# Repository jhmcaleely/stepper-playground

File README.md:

# stepper-playground

A scratch project to explore stepper motor control

Currently depends on:

- Pololu 2134, a carrier board for DRV8834 Stepper Driver
- Raspberry Pi Pico
- MicroPython

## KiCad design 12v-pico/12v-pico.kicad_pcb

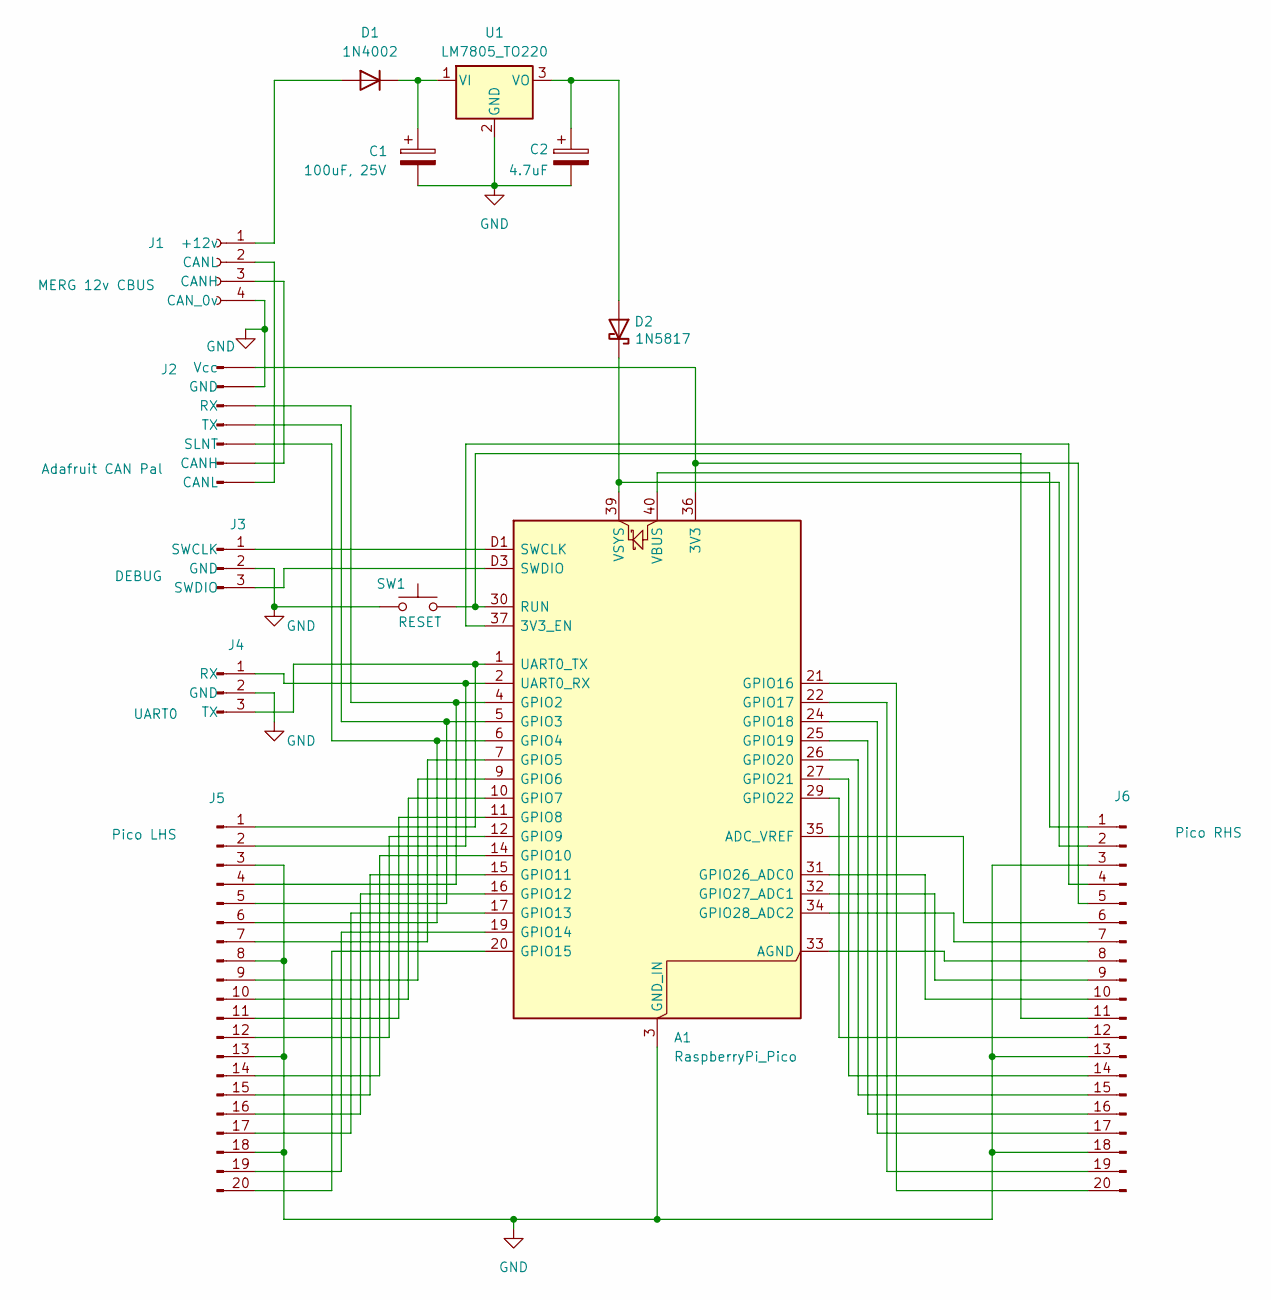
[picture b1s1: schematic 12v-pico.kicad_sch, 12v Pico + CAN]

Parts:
A1: RaspberryPi_Pico; RaspberryPi_Pico_SMD_HandSolder
C1: 100uF, 25V; CP_Radial_D4.0mm_P2.00mm
C2: 4.7uF; CP_Radial_Tantal_D4.5mm_P2.50mm
D1: 1N4002; D_DO-41_SOD81_P10.16mm_Horizontal
D2: 1N5817; D_DO-41_SOD81_P10.16mm_Horizontal
J1: MERG 12v CBUS; TerminalBlock_Phoenix_PT-1,5-4-3.5-H_1x04_P3.50mm_Horizontal
J2: Adafruit CAN Pal; PinHeader_1x07_P2.54mm_Vertical
J3: DEBUG; PinHeader_1x03_P2.54mm_Vertical
J4: UART0; PinSocket_1x03_P2.54mm_Vertical
J5: Pico LHS; PinHeader_1x20_P2.54mm_Vertical
J6: Pico RHS; PinHeader_1x20_P2.54mm_Vertical
SW1: RESET; SW_PUSH_6mm
U1: LM7805_TO220; TO-220-3_Vertical

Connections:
GND: A1.3 (GND_IN), A1.8 (GND), A1.13 (GND), A1.18 (GND), A1.23 (GND), A1.28 (GND), A1.38 (GND), A1.D2 (GND), C1.2, C2.2, J1.4 (CAN_0v), J2.2 (GND), J3.2 (GND), J4.2 (GND), J5.3, J5.8, J5.13, J5.18, J6.3, J6.13, J6.18, SW1.1, U1.2 (GND)
unnamed: A1.36 (3V3), J2.1 (Vcc), J6.5
unnamed: A1.37 (3V3_EN), J6.4
unnamed: A1.35 (ADC_VREF), J6.6
unnamed: A1.33 (AGND), J6.8
unnamed: A1.1 (UART0_TX), J4.3 (TX), J5.1
unnamed: A1.2 (UART0_RX), J4.1 (RX), J5.2
unnamed: A1.4 (GPIO2), J2.3 (RX), J5.4
unnamed: A1.5 (GPIO3), J2.4 (TX), J5.5
unnamed: A1.6 (GPIO4), J2.5 (SLNT), J5.6
unnamed: A1.7 (GPIO5), J5.7
unnamed: A1.9 (GPIO6), J5.9
unnamed: A1.10 (GPIO7), J5.10
unnamed: A1.11 (GPIO8), J5.11
unnamed: A1.12 (GPIO9), J5.12
unnamed: A1.14 (GPIO10), J5.14
unnamed: A1.15 (GPIO11), J5.15
unnamed: A1.16 (GPIO12), J5.16
unnamed: A1.17 (GPIO13), J5.17
unnamed: A1.19 (GPIO14), J5.19
unnamed: A1.20 (GPIO15), J5.20
unnamed: A1.21 (GPIO16), J6.20
unnamed: A1.22 (GPIO17), J6.19
unnamed: A1.24 (GPIO18), J6.17
unnamed: A1.25 (GPIO19), J6.16
unnamed: A1.26 (GPIO20), J6.15
unnamed: A1.27 (GPIO21), J6.14
unnamed: A1.29 (GPIO22), J6.12
unnamed: A1.31 (GPIO26_ADC0), J6.10
unnamed: A1.32 (GPIO27_ADC1), J6.9
unnamed: A1.34 (GPIO28_ADC2), J6.7
unnamed: A1.30 (RUN), J6.11, SW1.2
unnamed: A1.D1 (SWCLK), J3.1 (SWCLK)
unnamed: A1.D3 (SWDIO), J3.3 (SWDIO)
unnamed: A1.40 (VBUS), J6.1 (VBUS)
unnamed: A1.39 (VSYS), D2.1 (K), J6.2
unnamed: D1.2 (A), J1.1 (+12v)
unnamed: C1.1, D1.1 (K), U1.1 (VI)
unnamed: C2.1, D2.2 (A), U1.3 (VO)
unnamed: J1.3 (CANH), J2.6 (CANH)
unnamed: J1.2 (CANL), J2.7 (CANL)

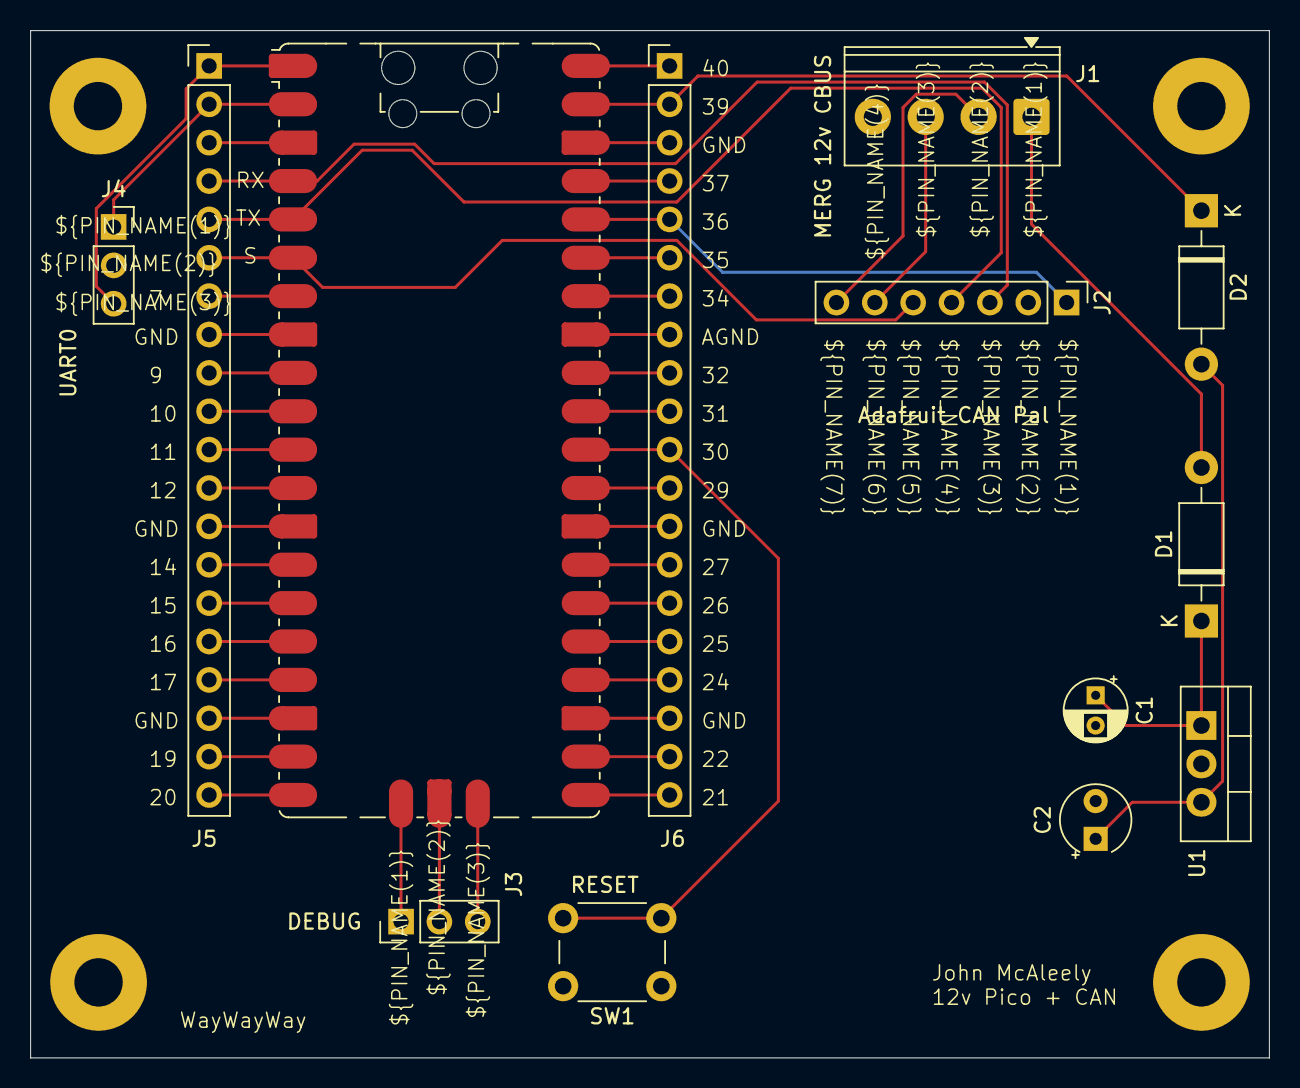
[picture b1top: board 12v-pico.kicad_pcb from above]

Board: 2 copper layers, 82.0 x 68.0 mm, 13 parts (0 on the bottom side), 41 nets.

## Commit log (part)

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2022-10-16 Initial code commit
    - Fix copyright to use my name
    - Describe project
    - Initial code that demos stepper control
2022-10-16 vscode-pymaker support
    add metadata for vscode-pymaker support
2024-03-04 board test files
2024-03-04 an old async test file
2024-07-22 misc hacks
2025-04-14 draft of can 12v pico for CBUS
2025-04-15 tidied up schematic
2025-04-16 design updates
2025-04-16 complies with design rules
2025-04-17 update symbols and labels
2025-04-17 even out board dimensions, label PCB
2025-04-17 made first gerbers from design
2025-11-05 c 2209 playground
2025-11-07 moving the stepper
2025-11-07 example uart pio
2025-11-07 rename
2025-11-07 lots of renaming
2025-11-07 more renaming
2025-11-07 maybe send 4 bytes via uart
2025-11-07 random refactoring
2025-11-07 maybe exchange request/reply
2025-11-07 renaming
2025-11-07 some gentle refactoring
2025-11-07 misc comments
2025-11-07 misc stuff
2025-11-07 mostly comments
2025-11-11 random shit
2025-11-11 its alive!
2025-11-11 can see bit change!
2025-11-11 uniform baudrate choices
2025-11-11 remove cruft
2025-11-11 some read request structure
2025-11-12 tidy up, now reads and writes registers
2025-11-12 working, doing stuff
2025-11-12 tidy up
2025-11-12 more tidy up
2025-12-07 correct test for success!
2025-12-07 max speed with this code
2025-12-07 remove non working uart PIO
2025-12-07 non-working pio
2025-12-07 slower, still not working
2025-12-07 working!
2025-12-07 move set pindir to setup
2026-01-21 wiring photo
2026-01-25 init a pulse length pio program
